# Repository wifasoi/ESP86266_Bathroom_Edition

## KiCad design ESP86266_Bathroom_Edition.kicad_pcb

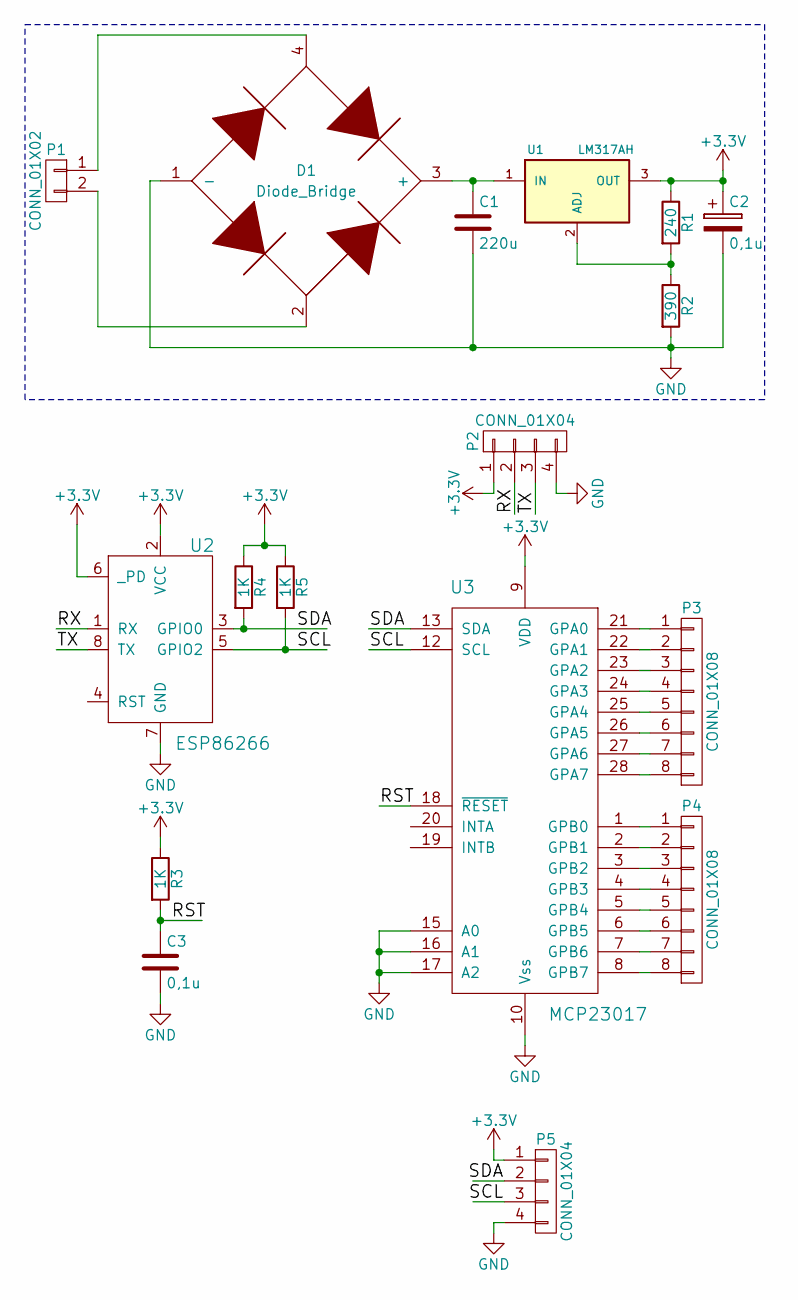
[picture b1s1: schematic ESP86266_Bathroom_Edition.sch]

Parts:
C1: 220u; c_elec_8x10
C2, C3: 0,1u; C_0805_HandSoldering
D1: Diode_Bridge; TO-12_TO-33_4Pin
P1: CONN_01X02; Pin_Header_Straight_1x02
P2: CONN_01X04; Socket_Strip_Angled_1x04
P3, P4: CONN_01X08; Pin_Header_Straight_1x08
P5: CONN_01X04; Pin_Header_Angled_1x04
R1: 240; R_0805_HandSoldering
R2: 390; R_0805_HandSoldering
R3, R4, R5: 1K; R_0805_HandSoldering
U1: LM317AH; SOT126_SOT32_Housing_Horizontal
U2: ESP86266; Socket_Strip_Straight_2x04
U3: MCP23017; SOIC-28_7.5x17.9mm_Pitch1.27mm

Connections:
+3V3: C2.1, P2.1, P5.1, R1.1, R3.1, R4.1, R5.1, U1.3 (OUT), U2.2 (VCC), U2.6 (_PD), U3.9 (VDD)
/RST: C3.1, R3.2, U3.18 (~RESET)
/RX: P2.2, U2.1 (RX)
/SCL: P5.3, R5.2, U2.5 (GPIO2), U3.12 (SCL)
/SDA: P5.2, R4.2, U2.3 (GPIO0), U3.13 (SDA)
/TX: P2.3, U2.8 (TX)
GND: C1.2, C2.2, C3.2, D1.1 (-), P2.4, P5.4, R2.2, U2.7 (GND), U3.10 (Vss), U3.15 (A0), U3.16 (A1), U3.17 (A2)
unnamed: C1.1, D1.3 (+), U1.1 (IN)
unnamed: D1.2, P1.2
unnamed: D1.4, P1.1
unnamed: P3.1, U3.21 (GPA0)
unnamed: P3.2, U3.22 (GPA1)
unnamed: P3.3, U3.23 (GPA2)
unnamed: P3.4, U3.24 (GPA3)
unnamed: P3.5, U3.25 (GPA4)
unnamed: P3.6, U3.26 (GPA5)
unnamed: P3.7, U3.27 (GPA6)
unnamed: P3.8, U3.28 (GPA7)
unnamed: P4.1, U3.1 (GPB0)
unnamed: P4.2, U3.2 (GPB1)
unnamed: P4.3, U3.3 (GPB2)
unnamed: P4.4, U3.4 (GPB3)
unnamed: P4.5, U3.5 (GPB4)
unnamed: P4.6, U3.6 (GPB5)
unnamed: P4.7, U3.7 (GPB6)
unnamed: P4.8, U3.8 (GPB7)
unnamed: R1.2, R2.1, U1.2 (ADJ)

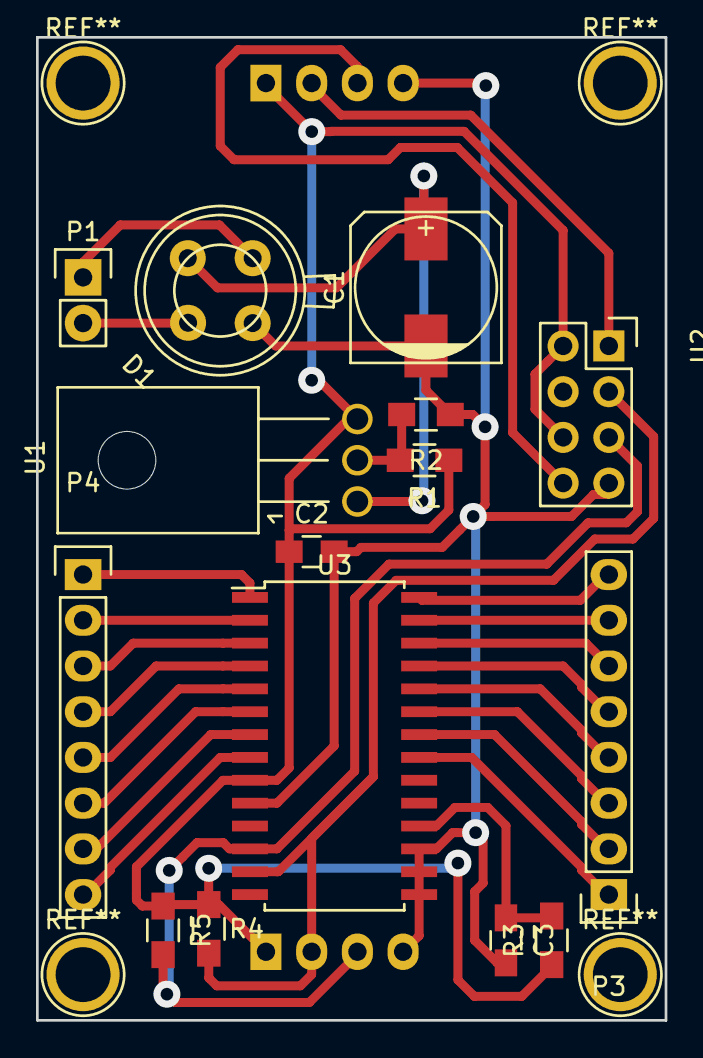
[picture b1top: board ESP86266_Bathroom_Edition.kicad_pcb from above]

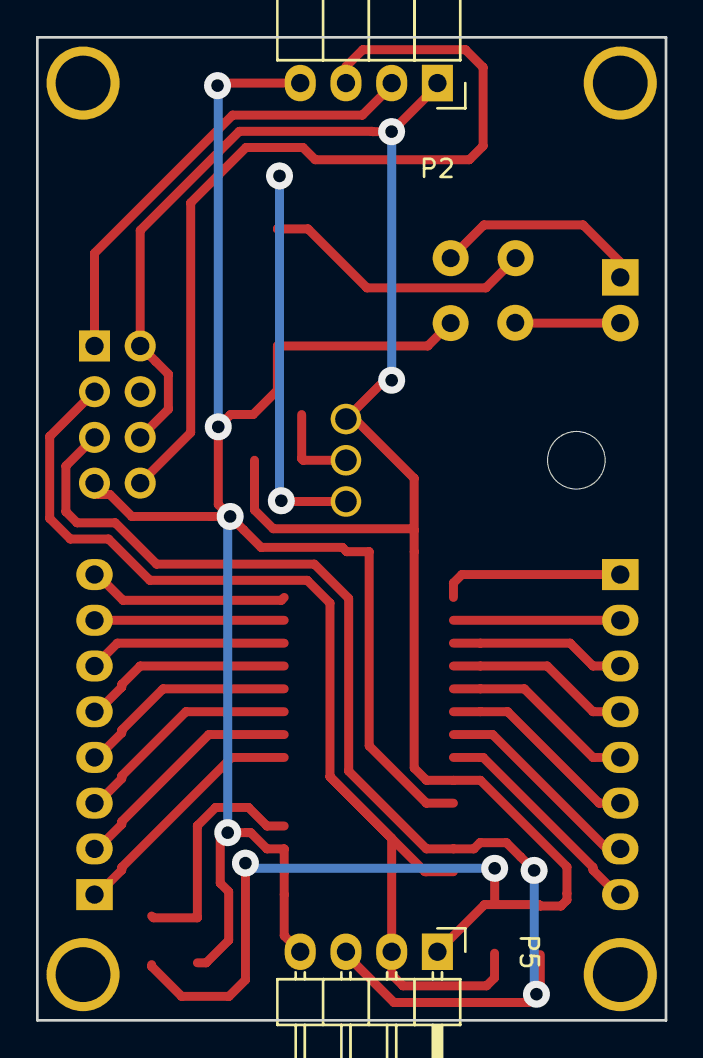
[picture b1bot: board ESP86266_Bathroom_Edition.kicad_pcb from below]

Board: 2 copper layers, 34.9 x 54.6 mm, 17 parts (2 on the bottom side), 27 nets.

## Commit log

2015-11-16 Firs version of the board
2015-11-16 Second version, added M3 mounting holes
